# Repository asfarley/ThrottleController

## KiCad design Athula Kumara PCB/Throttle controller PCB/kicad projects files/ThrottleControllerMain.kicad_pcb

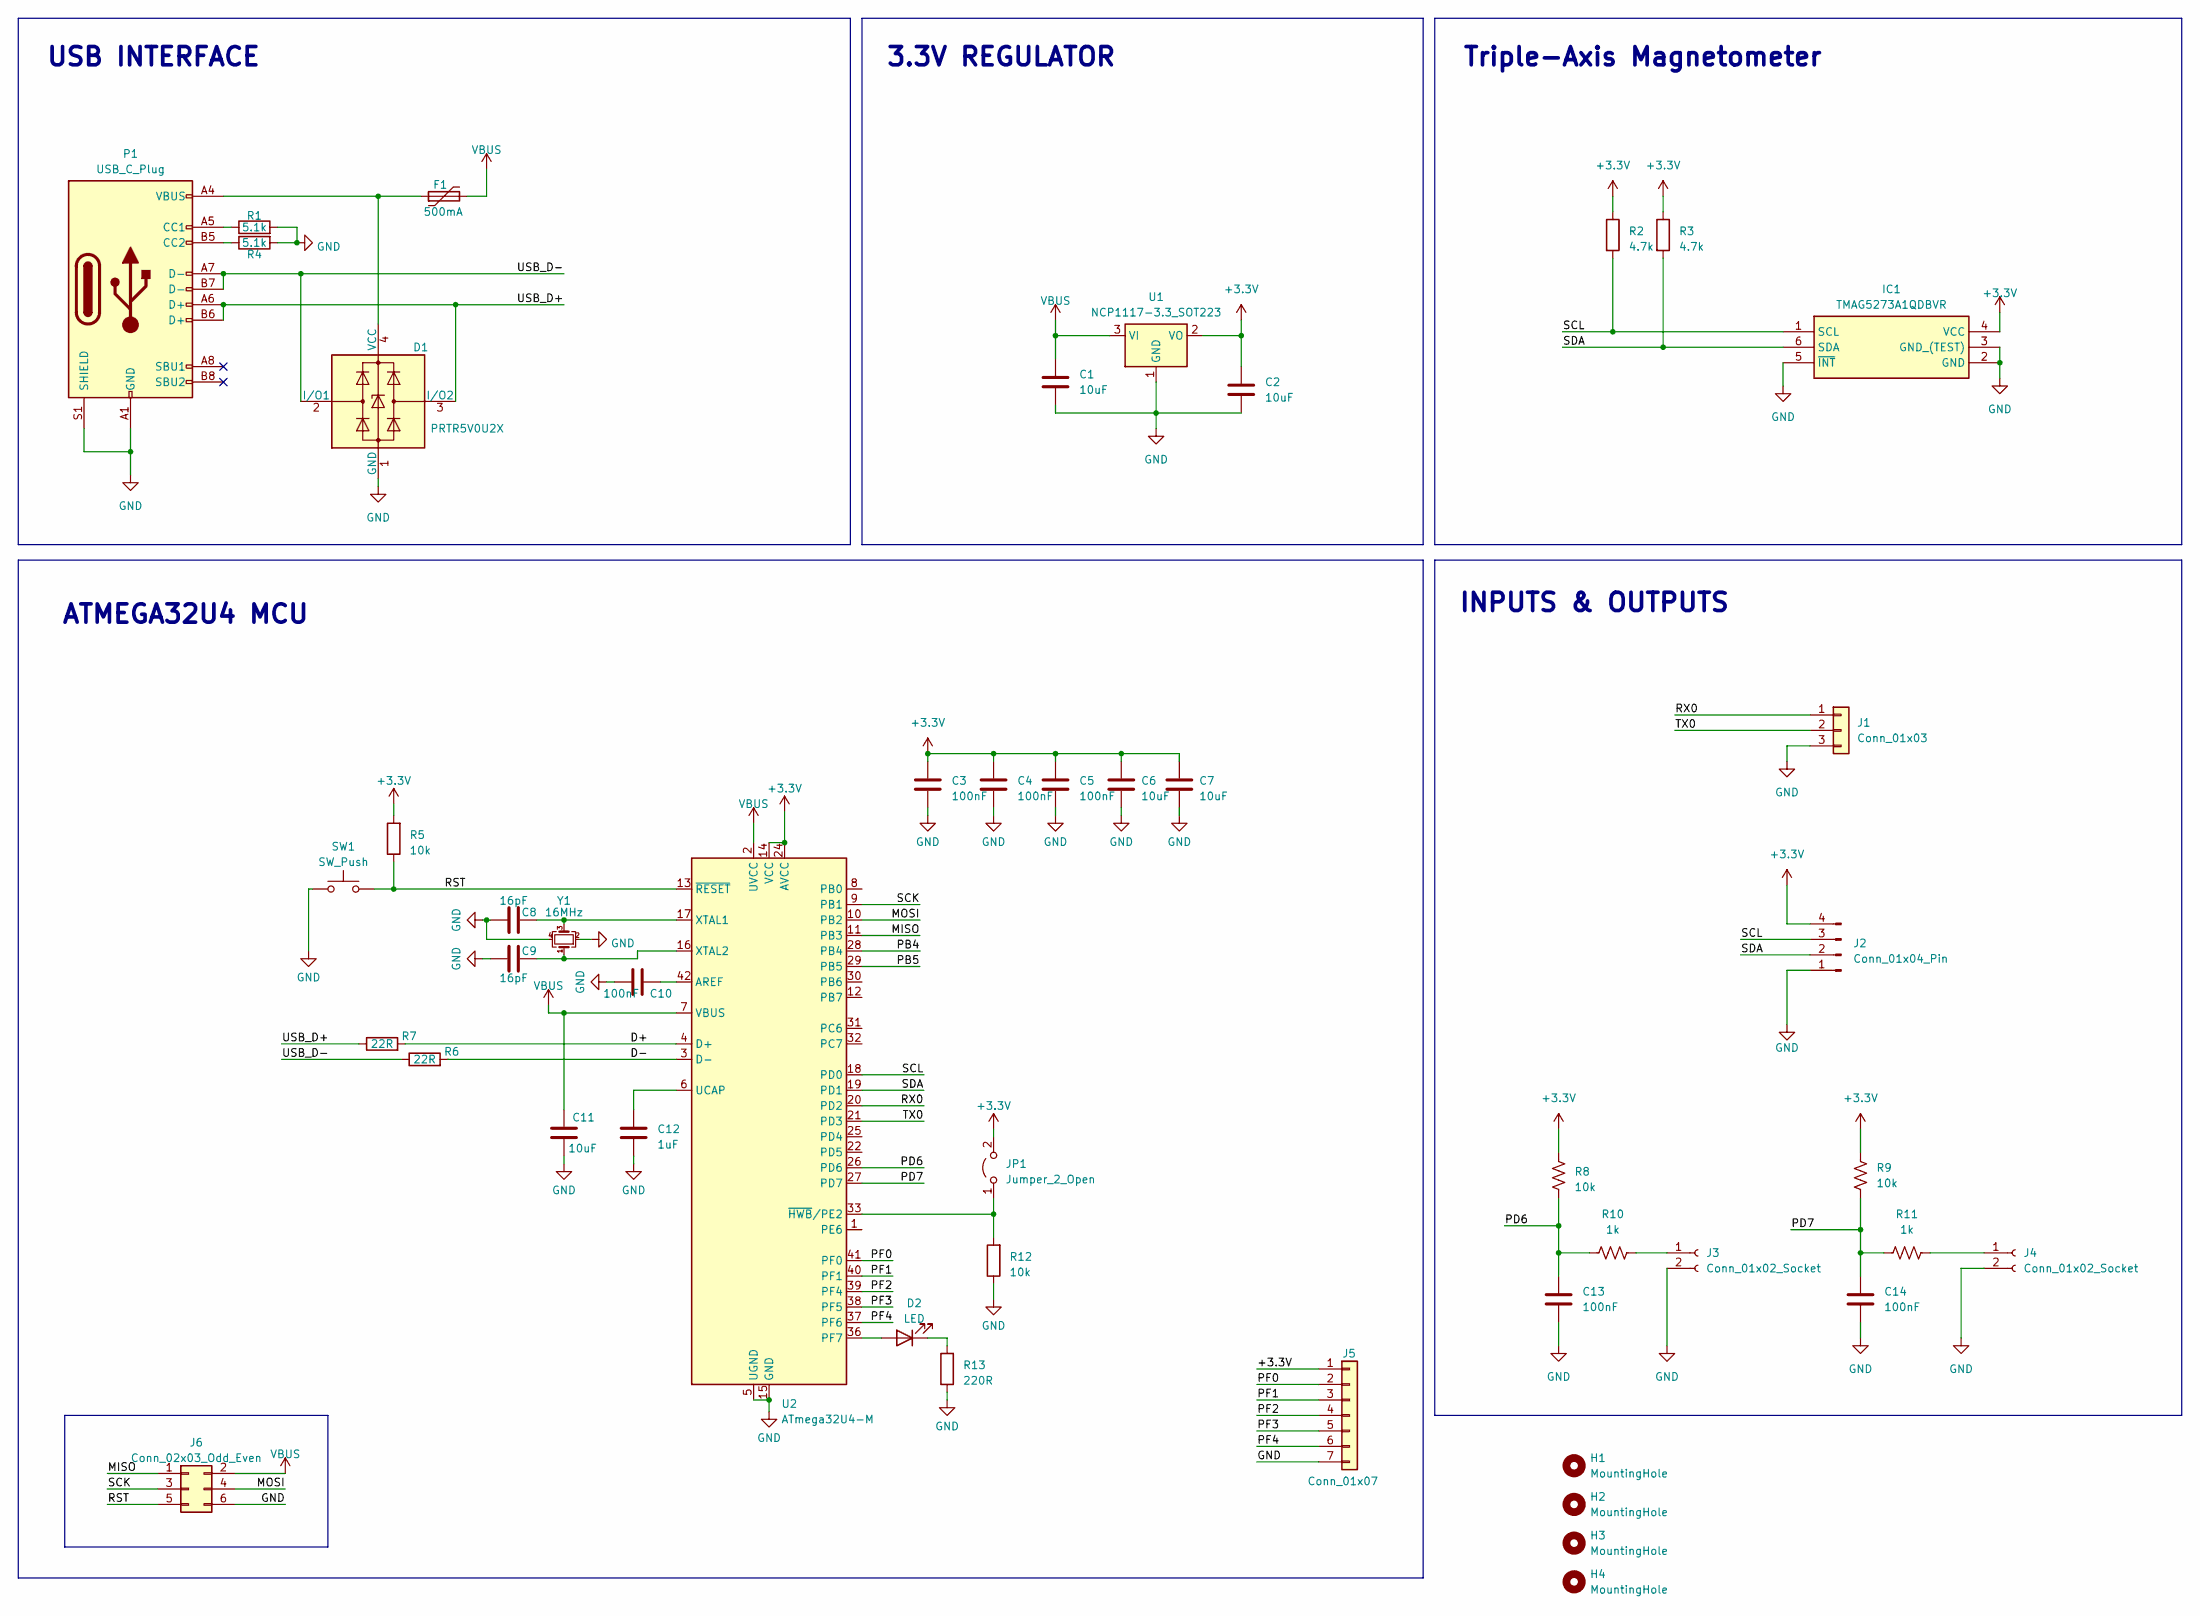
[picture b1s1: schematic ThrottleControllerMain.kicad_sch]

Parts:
C1, C2, C6, C7, C11: 10uF; C_0603_1608Metric; MPN CL10A106MA8NRNC
C3, C4, C5, C10, C13, C14: 100nF; C_0402_1005Metric; MPN CL05B104KO5NNNC
C8, C9: 16pF; C_0402_1005Metric; MPN GRM1555C1H160JA01D
C12: 1uF; C_0402_1005Metric; MPN CL05A105KO5NNNC
D1: PRTR5V0U2X; SOT-143; MPN PRTR5V0U2X,215
D2: LED; LED_0402_1005Metric; MPN TZ-P2-0402 0TIA1-0.45T
F1: 500mA; Fuse_0805_2012Metric; MPN 0805L050WR; Mouser_PN 576-0805L050
H1, H2, H3, H4: MountingHole; MountingHole_3.2mm_M3; MPN NA
IC1: TMAG5273A1QDBVR; SOT-23-6; Mouser Part Number 595-TMAG5273A1QDBVR
J1: Conn_01x03; PinHeader_1x03_P2.54mm_Vertical; MPN C49257
J2: Conn_01x04_Pin; JST_SH_BM04B-SRSS-TB_1x04-1MP_P1.00mm_Vertical; MPN BM04B-SRSS-TB(LF)(SN)
J3, J4: Conn_01x02_Socket; JST_SH_BM02B-SRSS-TB_1x02-1MP_P1.00mm_Vertical; MPN BM02B-SRSS-TB(LF)(SN)
J5: Conn_01x07; PinSocket_1x07_P2.54mm_Vertical_SMD_Pin1Right; MPN DNP
J6: Conn_02x03_Odd_Even; PinHeader_2x03_P2.54mm_Vertical; MPN DNP
JP1: Jumper_2_Open; SolderJumper-2_P1.3mm_Open_RoundedPad1.0x1.5mm; MPN DNP
P1: USB_C_Plug; USB_C_Receptacle_G-Switch_GT-USB-7010ASV; MPN GT-USB-7010ASV
R1, R4: 5.1k; R_0402_1005Metric; MPN RC0402FR-075K1L
R2, R3: 4.7k; R_0402_1005Metric; MPN RC0402FR-074K7L
R5, R8, R9, R12: 10k; R_0402_1005Metric; MPN RC0402FR-0710KL
R6, R7: 22R; R_0402_1005Metric; MPN RC0402FR-0722RL
R10, R11: 1k; R_0402_1005Metric; MPN RC0402FR-071KL
R13: 220R; R_0402_1005Metric; MPN RC0402FR-0722RL
SW1: SW_Push; Panasonic_EVQPUJ_EVQPUA; MPN EVQ-PUA02K
U1: NCP1117-3.3_SOT223; SOT-223-3_TabPin2; MPN NCP1117ST33T3G
U2: ATmega32U4-M; QFN-44-1EP_7x7mm_P0.5mm_EP5.2x5.2mm; MPN ATMEGA32U4-MU
Y1: 16MHz; Crystal_SMD_3225-4Pin_3.2x2.5mm; MPN TAXM16M4RFBCCT2T

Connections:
+3.3V: C2.1, C3.2, C4.2, C5.2, C6.2, C7.2, IC1.4 (VCC), J2.4, J5.1, JP1.2 (B), R2.1, R3.1, R5.2, R8.1, R9.1, U1.2 (VO), U2.14 (VCC), U2.24 (AVCC), U2.34 (VCC), U2.44 (AVCC)
/D+: R7.2, U2.4 (D+)
/D-: R6.2, U2.3 (D-)
/MISO: J6.1, U2.11 (PB3)
/MOSI: J6.4, U2.10 (PB2)
/PB4: U2.28 (PB4)
/PB5: U2.29 (PB5)
/PD6: C13.1, R8.2, R10.1, U2.26 (PD6)
/PD7: C14.1, R9.2, R11.1, U2.27 (PD7)
/PF0: J5.2, U2.41 (PF0)
/PF1: J5.3, U2.40 (PF1)
/PF2: J5.4, U2.39 (PF4)
/PF3: J5.5, U2.38 (PF5)
/PF4: J5.6, U2.37 (PF6)
/RST: J6.5, R5.1, SW1.2, U2.13 (~RESET)
/RX0: J1.1, U2.20 (PD2)
/SCK: J6.3, U2.9 (PB1)
/SCL: IC1.1 (SCL), J2.3, R2.2, U2.18 (PD0)
/SDA: IC1.6 (SDA), J2.2, R3.2, U2.19 (PD1)
/TX0: J1.2, U2.21 (PD3)
/USB_D+: D1.3 (I/O2), P1.A6 (D+), P1.B6 (D+), R7.1
/USB_D-: D1.2 (I/O1), P1.A7 (D-), P1.B7 (D-), R6.1
GND: C1.2, C2.2, C3.1, C4.1, C5.1, C6.1, C7.1, C8.1, C9.1, C10.1, C11.2, C12.1, C13.2, C14.2, D1.1 (GND), IC1.2 (GND), IC1.3 (GND_(TEST)), IC1.5 (~INT), J1.3, J2.1, J3.2, J4.2, J5.7, J6.6, P1.A1 (GND), P1.A12 (GND), P1.B1 (GND), P1.B12 (GND), P1.S1 (SHIELD), R1.2, R4.2, R12.1, R13.1, SW1.1, U1.1 (GND), U2.5 (UGND), U2.15 (GND), U2.23 (GND), U2.35 (GND), U2.43 (GND), U2.45 (GND), Y1.2, Y1.4
unnamed: D1.4 (VCC), F1.1, P1.A4 (VBUS), P1.A9 (VBUS), P1.B4 (VBUS), P1.B9 (VBUS)
unnamed: D2.2 (A), U2.36 (PF7)
unnamed: D2.1 (K), R13.2
unnamed: J3.1, R10.2
unnamed: J4.1, R11.2
unnamed: JP1.1 (A), R12.2, U2.33 (~HWB/PE2)
unnamed: P1.A5 (CC1), R1.1
unnamed: P1.B5 (CC2), R4.1
unnamed: C10.2, U2.42 (AREF)
unnamed: C12.2, U2.6 (UCAP)
unnamed: C8.2, U2.17 (XTAL1), Y1.3
unnamed: C9.2, U2.16 (XTAL2), Y1.1
VBUS: C1.1, C11.1, F1.2, J6.2, U1.3 (VI), U2.2 (UVCC), U2.7 (VBUS)

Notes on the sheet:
USB INTERFACE
ATMEGA32U4 MCU
Triple-Axis Magnetometer
3.3V REGULATOR
INPUTS & OUTPUTS

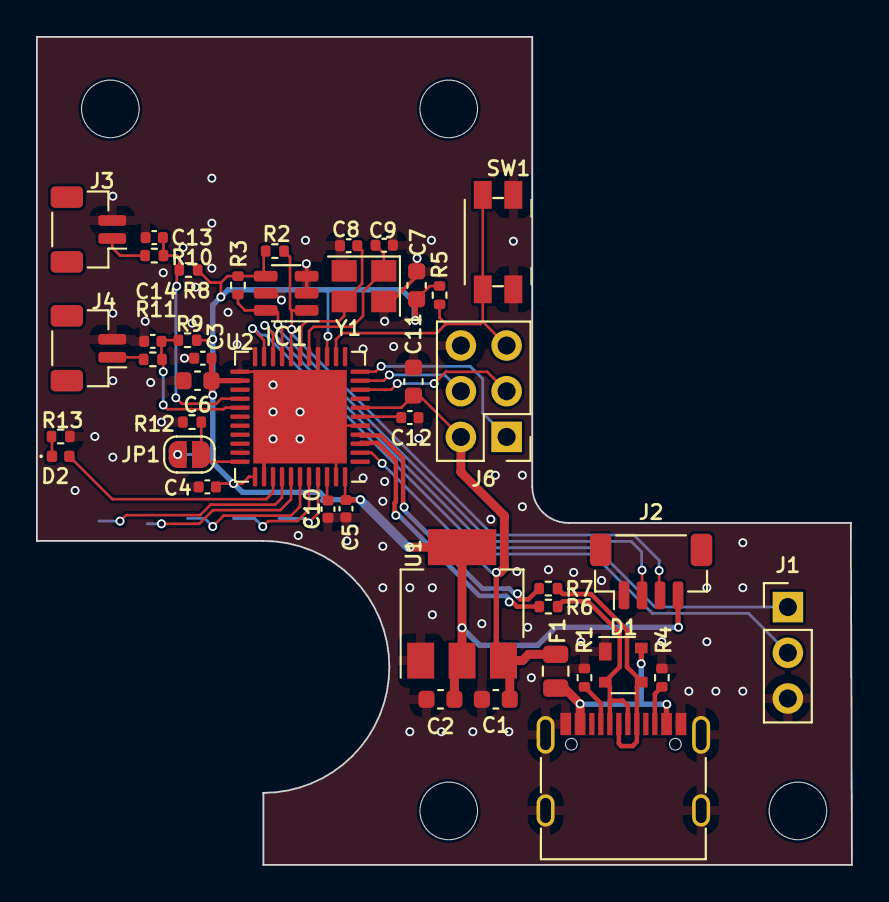
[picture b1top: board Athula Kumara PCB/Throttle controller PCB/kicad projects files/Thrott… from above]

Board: 2 copper layers, 45.3 x 46.0 mm, 47 parts (1 on the bottom side), 34 nets.

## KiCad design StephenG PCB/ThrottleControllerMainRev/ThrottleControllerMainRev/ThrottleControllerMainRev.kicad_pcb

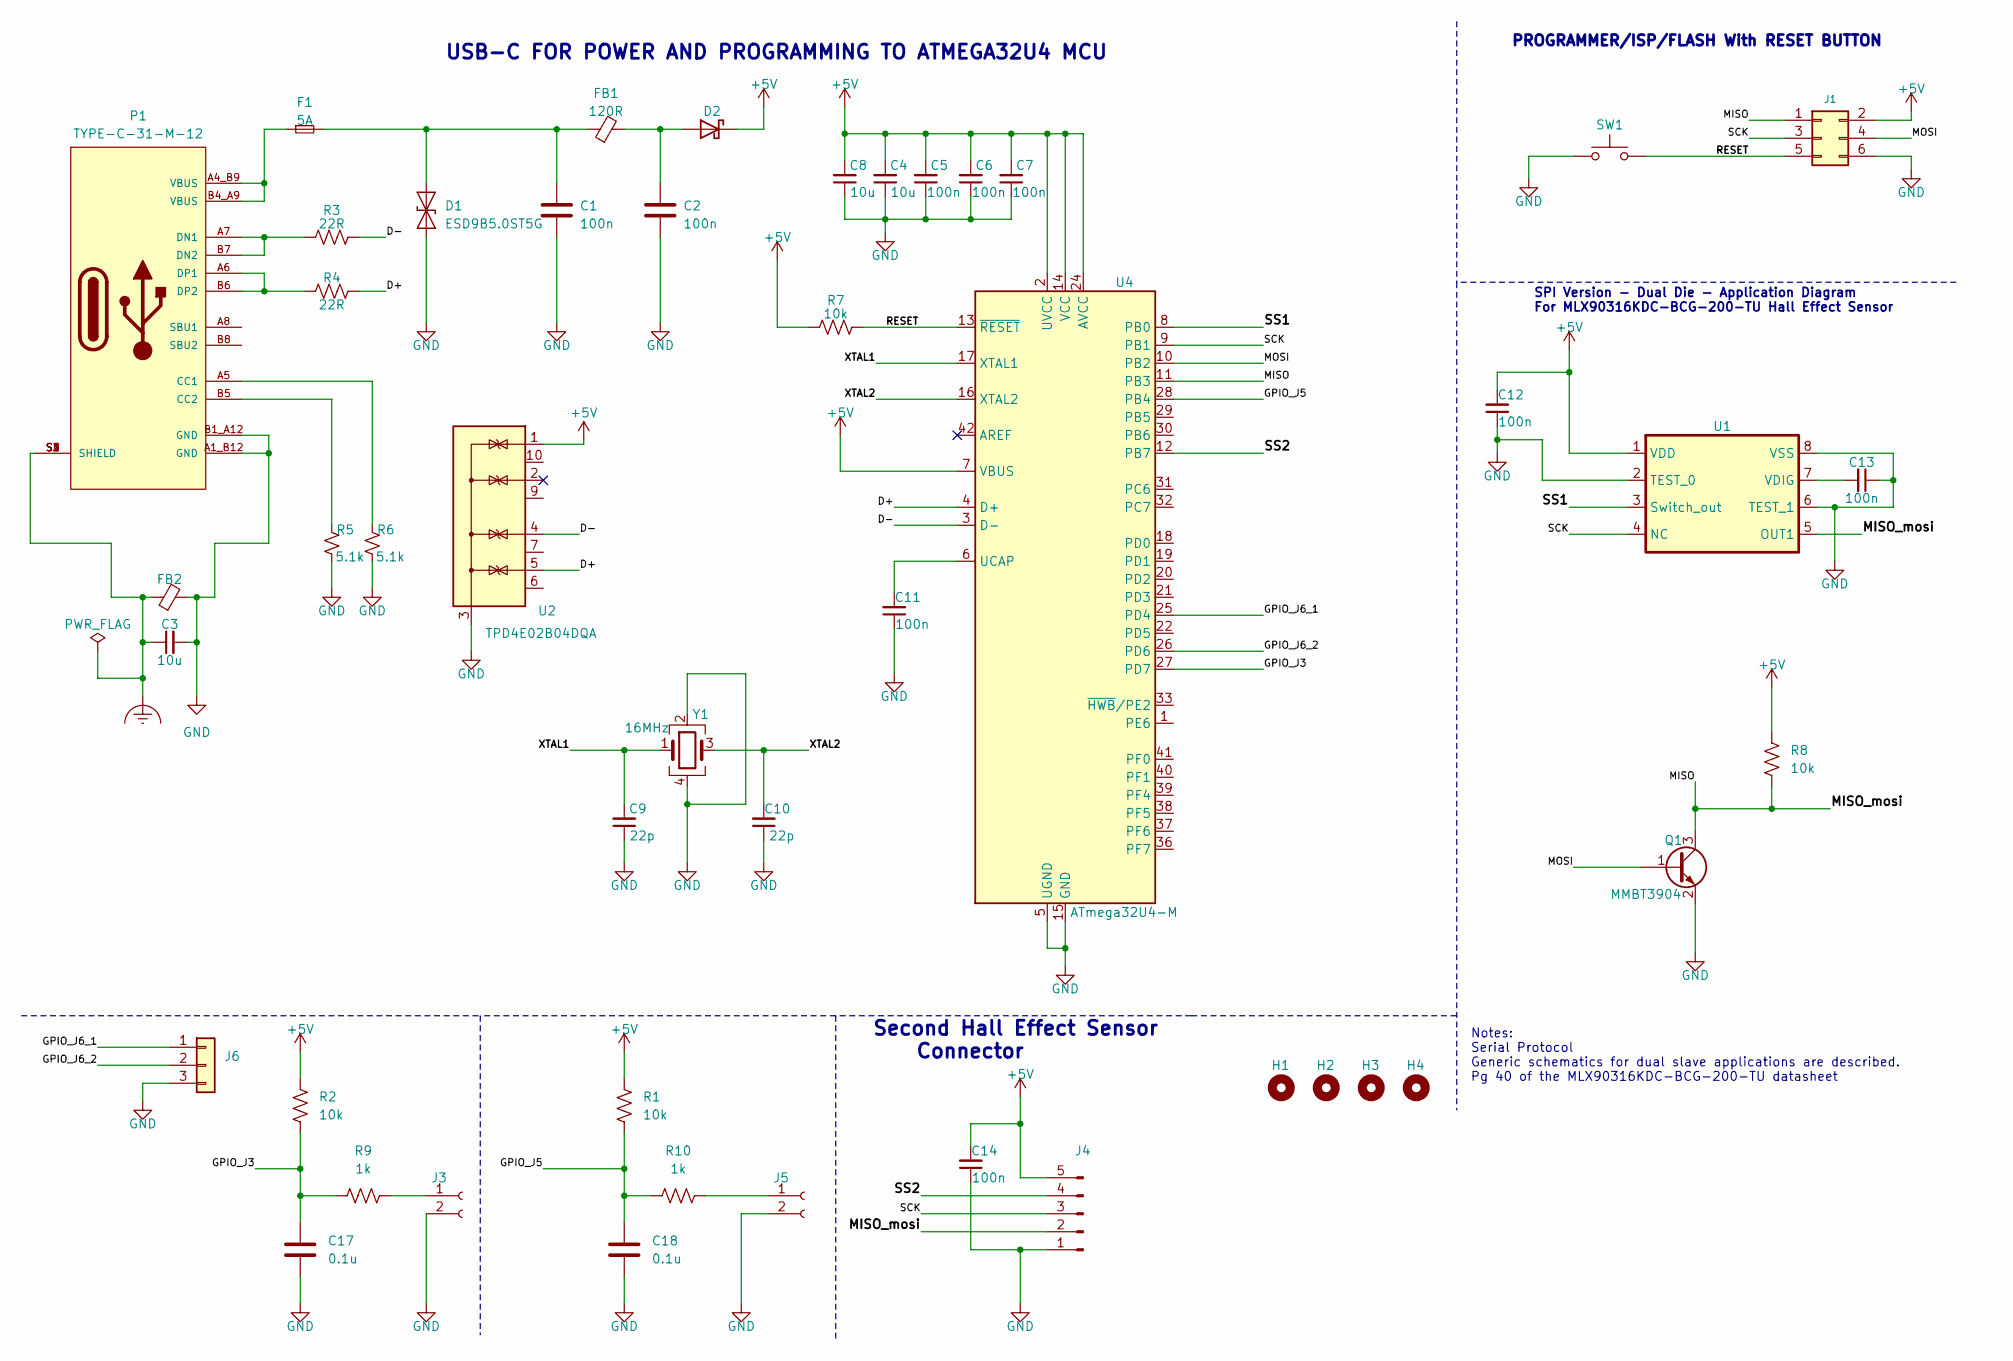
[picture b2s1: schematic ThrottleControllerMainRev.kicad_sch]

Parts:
C1, C2, C5, C6, C7, C11, C12, C13, C14: 100n; C_0603_1608Metric
C3, C4, C8: 10u; C_0603_1608Metric
C9, C10: 22p; C_0402_1005Metric
C17, C18: 0.1u; C_0603_1608Metric
D1: ESD9B5.0ST5G; D_SOD-923
D2: D_Schottky; D_SOD-123
F1: 5A; Fuse_1206_3216Metric
FB1: 120R; L_0603_1608Metric
FB2: FerriteBead_Small; L_0603_1608Metric
H1, H2, H3, H4: MountingHole; MountingHole_3.2mm_M3
J1: Conn_02x03_Odd_Even; PinHeader_2x03_P2.54mm_Vertical
J3, J5: Conn_01x02_Socket; JST_SH_BM02B-SRSS-TB_1x02-1MP_P1.00mm_Vertical
J4: Conn_01x04_Pin; JST_SH_BM05B-SRSS-TB_1x05-1MP_P1.00mm_Vertical
J6: Conn_01x03; PinHeader_1x03_P2.54mm_Vertical
P1: TYPE-C-31-M-12; HRO_TYPE-C-31-M-12; PARTREV 2020.12.08
Q1: MMBT3904; SOT-23
R1, R2, R7, R8: 10k; R_0603_1608Metric
R3, R4: 22R; R_0603_1608Metric
R5, R6: 5.1k; R_0603_1608Metric
R9, R10: 1k; R_0603_1608Metric
SW1: SW_Push; SW_SPST_B3U-1000P-B
U1: SOIC127P600X172-8N
U2: TPD4E02B04DQA; USON-10_2.5x1.0mm_P0.5mm
U4: ATmega32U4-M; QFN-44-1EP_7x7mm_P0.5mm_EP5.2x5.2mm
Y1: 16MHz; Crystal_SMD_3225-4Pin_3.2x2.5mm

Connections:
+5V: C4.2, C5.2, C6.2, C7.2, C8.2, C12.2, C14.2, D2.1 (K), J1.2, J4.5, R1.1, R2.1, R7.1, R8.1, U1.1 (VDD), U2.1 (IO1), U4.2 (UVCC), U4.7 (VBUS), U4.14 (VCC), U4.24 (AVCC), U4.34 (VCC), U4.44 (AVCC)
/D+: R4.2, U2.5 (IO4), U4.4 (D+)
/D-: R3.2, U2.4 (IO3), U4.3 (D-)
/GPIO_J3: C17.1, R2.2, R9.1, U4.27 (PD7)
/GPIO_J5: C18.1, R1.2, R10.1, U4.28 (PB4)
/GPIO_J6_1: J6.1, U4.25 (PD4)
/GPIO_J6_2: J6.2, U4.26 (PD6)
/MISO: J1.1, J4.2, Q1.3 (C), R8.2, U1.5 (OUT1), U4.11 (PB3)
/MOSI: J1.4, Q1.1 (B), U4.10 (PB2)
/RESET: J1.5, R7.2, SW1.2, U4.13 (~RESET)
/SCK: J1.3, J4.3, U1.4 (NC), U4.9 (PB1)
/SS1: U1.3 (Switch_out), U4.8 (PB0)
/SS2: J4.4, U4.12 (PB7)
/XTAL1: C9.2, U4.17 (XTAL1), Y1.1
/XTAL2: C10.2, U4.16 (XTAL2), Y1.3
Earth_Clean: C3.1, FB2.1, P1.S1 (SHIELD), P1.S2 (SHIELD), P1.S3 (SHIELD), P1.S4 (SHIELD)
GND: C1.2, C2.2, C3.2, C4.1, C5.1, C6.1, C7.1, C8.1, C9.1, C10.1, C11.1, C12.1, C13.1, C14.1, C17.2, C18.2, D1.1 (A1), FB2.2, J1.6, J3.2, J4.1, J5.2, J6.3, P1.A1_B12 (GND), P1.B1_A12 (GND), Q1.2 (E), R5.2, R6.2, SW1.1, U1.2 (TEST_0), U1.6 (TEST_1), U1.8 (VSS), U2.3 (G), U2.8 (G), U4.5 (UGND), U4.15 (GND), U4.23 (GND), U4.35 (GND), U4.43 (GND), U4.45 (GND), Y1.2, Y1.4
unnamed: C1.1, D1.2 (A2), F1.2, FB1.1
unnamed: C2.1, D2.2 (A), FB1.2
unnamed: F1.1, P1.A4_B9 (VBUS), P1.B4_A9 (VBUS)
unnamed: J3.1, R9.2
unnamed: J5.1, R10.2
unnamed: P1.A5 (CC1), R6.1
unnamed: P1.B5 (CC2), R5.1
unnamed: P1.A7 (DN1), P1.B7 (DN2), R3.1
unnamed: P1.A6 (DP1), P1.B6 (DP2), R4.1
unnamed: C13.2, U1.7 (VDIG)
unnamed: C11.2, U4.6 (UCAP)

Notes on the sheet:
Notes: Serial Protocol Generic schematics for dual slave applications are described. Pg 40 of the MLX90316KDC-BCG-200-TU datasheet
PROGRAMMER/ISP/FLASH With RESET BUTTON
USB-C FOR POWER AND PROGRAMMING TO ATMEGA32U4 MCU
Second Hall Effect Sensor Connector
SPI Version - Dual Die - Application Diagram For MLX90316KDC-BCG-200-TU Hall Effect Sensor

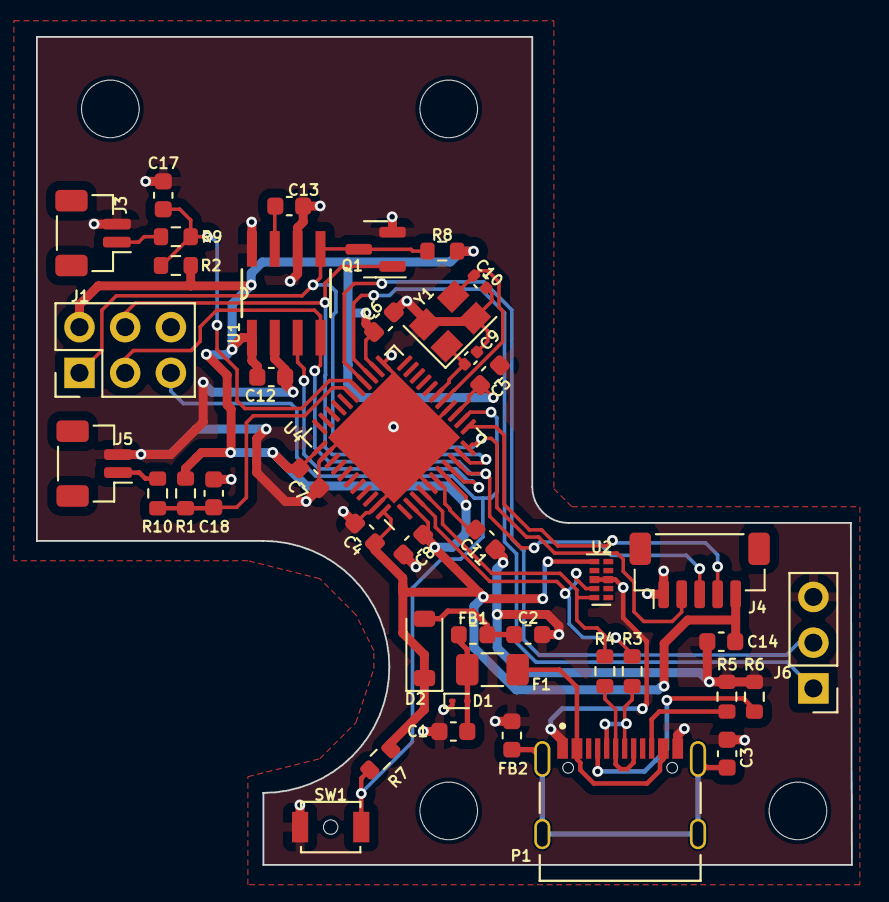
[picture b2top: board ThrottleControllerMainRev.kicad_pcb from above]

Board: 2 copper layers, 45.3 x 46.0 mm, 47 parts (0 on the bottom side), 28 nets.

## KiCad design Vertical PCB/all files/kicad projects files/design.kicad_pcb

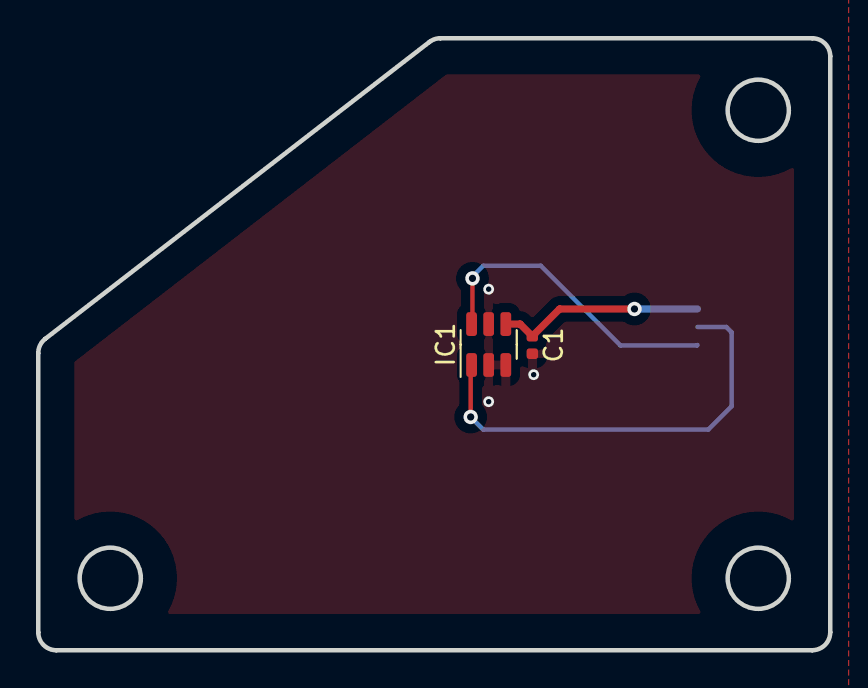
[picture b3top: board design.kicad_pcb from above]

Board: 2 copper layers, 44.0 x 34.0 mm, 3 parts (1 on the bottom side), 4 nets.

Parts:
C1: 100nF; C_0402_1005Metric
IC1: TMAG5273B1QDBVR; SOT-23-6
J1: Conn_01x04_Pin; JST_SH_SM04B-SRSS-TB_1x04-1MP_P1.00mm_Horizontal

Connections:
+3.3V: C1.1, IC1.4 (VCC), J1.1
/SCL: IC1.1 (SCL), J1.2
/SDA: IC1.6 (SDA), J1.3
GND: C1.2, IC1.2 (GND), IC1.3 (GND_(TEST)), IC1.5 (~INT), J1.4

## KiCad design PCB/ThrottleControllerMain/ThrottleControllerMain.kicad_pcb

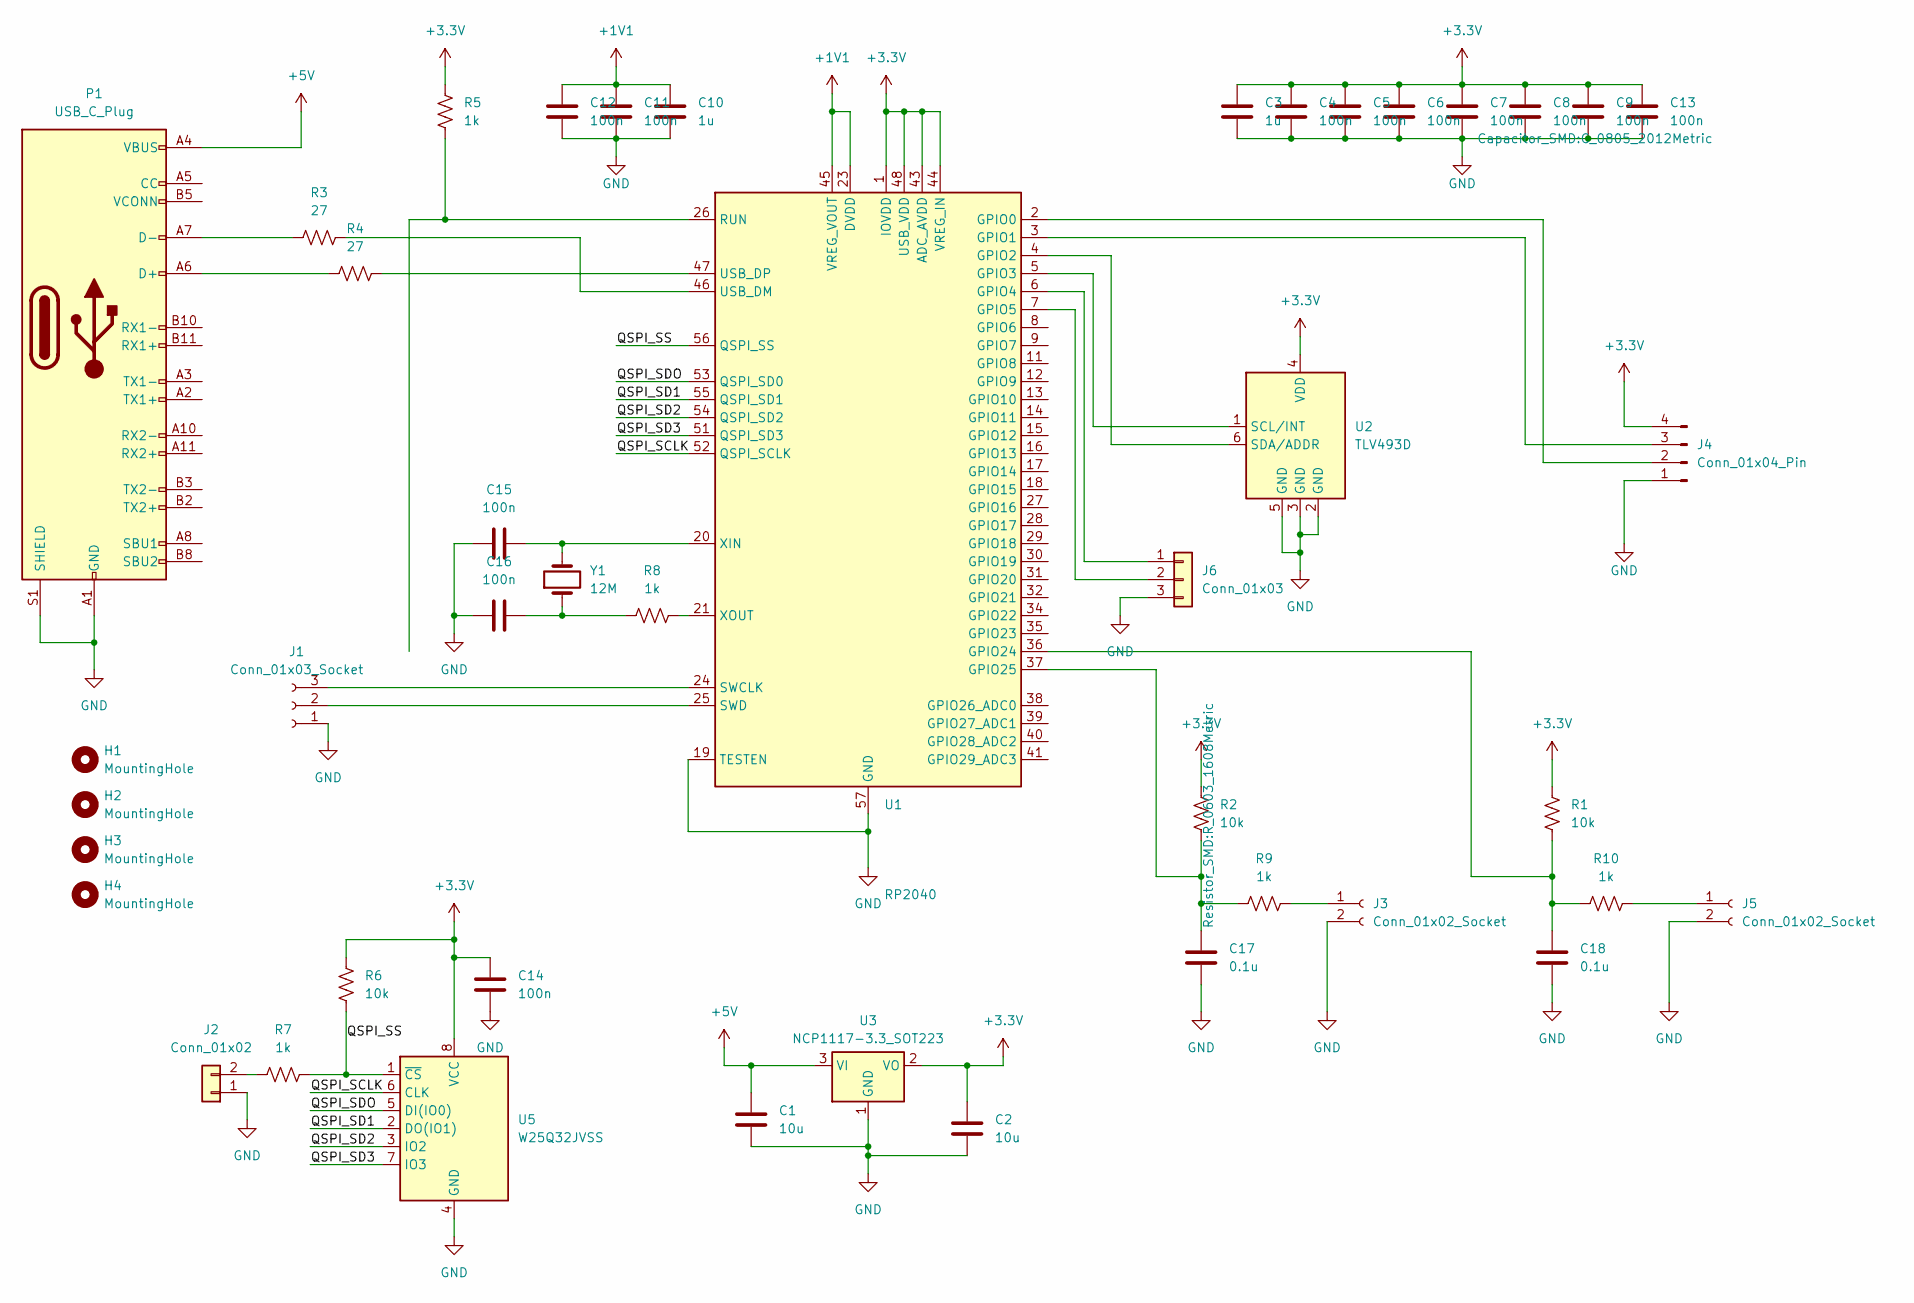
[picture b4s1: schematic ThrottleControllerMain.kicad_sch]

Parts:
C1, C2: 10u; C_0603_1608Metric
C3, C10: 1u; C_0402_1005Metric
C4, C5, C6, C7, C8, C9, C13: 100n; C_0805_2012Metric
C11, C12, C14, C15: 100n; C_0201_0603Metric
C16: 100n; C_0603_1608Metric
C17, C18: 0.1u; C_0603_1608Metric
H1, H2, H3, H4: MountingHole; MountingHole_3.2mm_M3
J1: Conn_01x03_Socket; JST_SH_BM03B-SRSS-TB_1x03-1MP_P1.00mm_Vertical
J2: Conn_01x02; PinHeader_1x02_P2.54mm_Vertical
J3, J5: Conn_01x02_Socket; JST_SH_BM02B-SRSS-TB_1x02-1MP_P1.00mm_Vertical
J4: Conn_01x04_Pin; JST_SH_BM04B-SRSS-TB_1x04-1MP_P1.00mm_Vertical
J6: Conn_01x03; PinHeader_1x03_P2.54mm_Vertical
P1: USB_C_Plug; USB_C_Receptacle_G-Switch_GT-USB-7010ASV
R1, R2, R6: 10k; R_0603_1608Metric
R3, R4: 27; R_0603_1608Metric
R5, R7, R8, R9, R10: 1k; R_0603_1608Metric
U1: RP2040; QFN-56-1EP_7x7mm_P0.4mm_EP3.2x3.2mm
U2: TLV493D; SOT-23-6
U3: NCP1117-3.3_SOT223; SOT-223-3_TabPin2
U5: W25Q32JVSS; SOIC-8_5.23x5.23mm_P1.27mm
Y1: 12M; Crystal_SMD_3225-4Pin_3.2x2.5mm

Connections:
+1V1: C10.1, C11.1, C12.1, U1.23 (DVDD), U1.45 (VREG_VOUT), U1.50 (DVDD)
+3.3V: C2.1, C3.1, C4.1, C5.1, C6.1, C7.1, C8.1, C9.1, C13.1, C14.1, J4.4, R1.1, R2.1, R5.1, R6.1, U1.1 (IOVDD), U1.10 (IOVDD), U1.22 (IOVDD), U1.33 (IOVDD), U1.42 (IOVDD), U1.43 (ADC_AVDD), U1.44 (VREG_IN), U1.48 (USB_VDD), U1.49 (IOVDD), U2.4 (VDD), U3.2 (VO), U5.8 (VCC)
+5V: C1.1, P1.A4 (VBUS), P1.A9 (VBUS), P1.B4 (VBUS), P1.B9 (VBUS), U3.3 (VI)
/QSPI_SCLK: U1.52 (QSPI_SCLK), U5.6 (CLK)
/QSPI_SD1: U1.55 (QSPI_SD1), U5.2 (DO(IO1))
/QSPI_SD2: U1.54 (QSPI_SD2), U5.3 (IO2)
/QSPI_SD3: U1.51 (QSPI_SD3), U5.7 (IO3)
/QSPI_SDO: U1.53 (QSPI_SD0), U5.5 (DI(IO0))
/QSPI_SS: R6.2, R7.2, U1.56 (QSPI_SS), U5.1 (~CS)
GND: C1.2, C2.2, C3.2, C4.2, C5.2, C6.2, C7.2, C8.2, C9.2, C10.2, C11.2, C12.2, C13.2, C14.2, C15.1, C16.1, C17.2, C18.2, J1.1, J2.1, J3.2, J4.1, J5.2, J6.3, P1.A1 (GND), P1.A12 (GND), P1.B1 (GND), P1.B12 (GND), P1.S1 (SHIELD), U1.19 (TESTEN), U1.57 (GND), U2.2 (GND), U2.3 (GND), U2.5 (GND), U3.1 (GND), U5.4 (GND)
unnamed: C16.2, R8.1, Y1.1
unnamed: J1.2, U1.25 (SWD)
unnamed: J1.3, U1.24 (SWCLK)
unnamed: J2.2, R7.1
unnamed: J3.1, R9.2
unnamed: J4.2, U1.2 (GPIO0)
unnamed: J4.3, U1.3 (GPIO1)
unnamed: J5.1, R10.2
unnamed: J6.1, U1.6 (GPIO4)
unnamed: J6.2, U1.7 (GPIO5)
unnamed: P1.A6 (D+), R4.1
unnamed: P1.A7 (D-), R3.1
unnamed: U1.4 (GPIO2), U2.6 (SDA/ADDR)
unnamed: U1.5 (GPIO3), U2.1 (SCL/INT)
unnamed: C18.1, R1.2, R10.1, U1.36 (GPIO24)
unnamed: C17.1, R2.2, R9.1, U1.37 (GPIO25)
unnamed: R5.2, U1.26 (RUN)
unnamed: R3.2, U1.46 (USB_DM)
unnamed: R4.2, U1.47 (USB_DP)
unnamed: C15.2, U1.20 (XIN), Y1.2
unnamed: R8.2, U1.21 (XOUT)

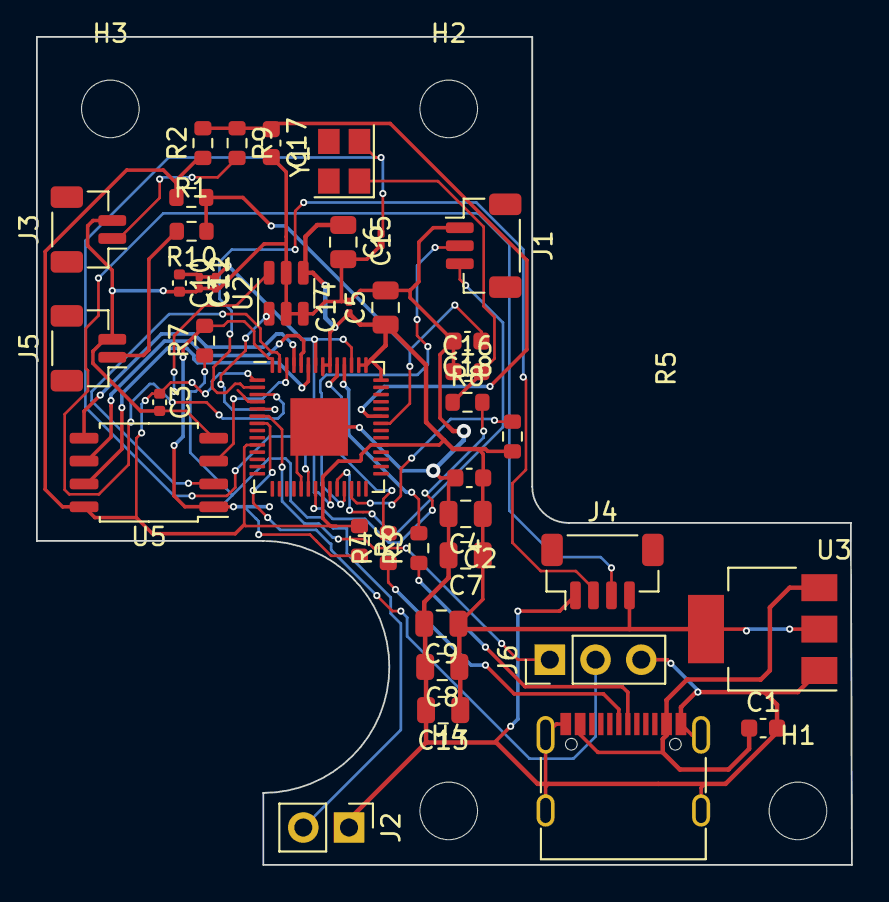
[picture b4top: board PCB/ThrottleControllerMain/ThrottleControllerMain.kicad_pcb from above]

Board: 2 copper layers, 45.3 x 46.0 mm, 44 parts (0 on the bottom side), 31 nets.

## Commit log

2023-10-25 CAD update
2023-10-25 Updating PCB
2023-10-26 PCB footprint layout is mostly complete.
2023-10-26 PCB positioning improvements
2023-10-26 Added serial-port debug header.
2023-10-27 Finished first draft of routing.
2023-10-27 Small edits to schematic
2026-03-21 Committing latest after building red powder-coated prototype.
